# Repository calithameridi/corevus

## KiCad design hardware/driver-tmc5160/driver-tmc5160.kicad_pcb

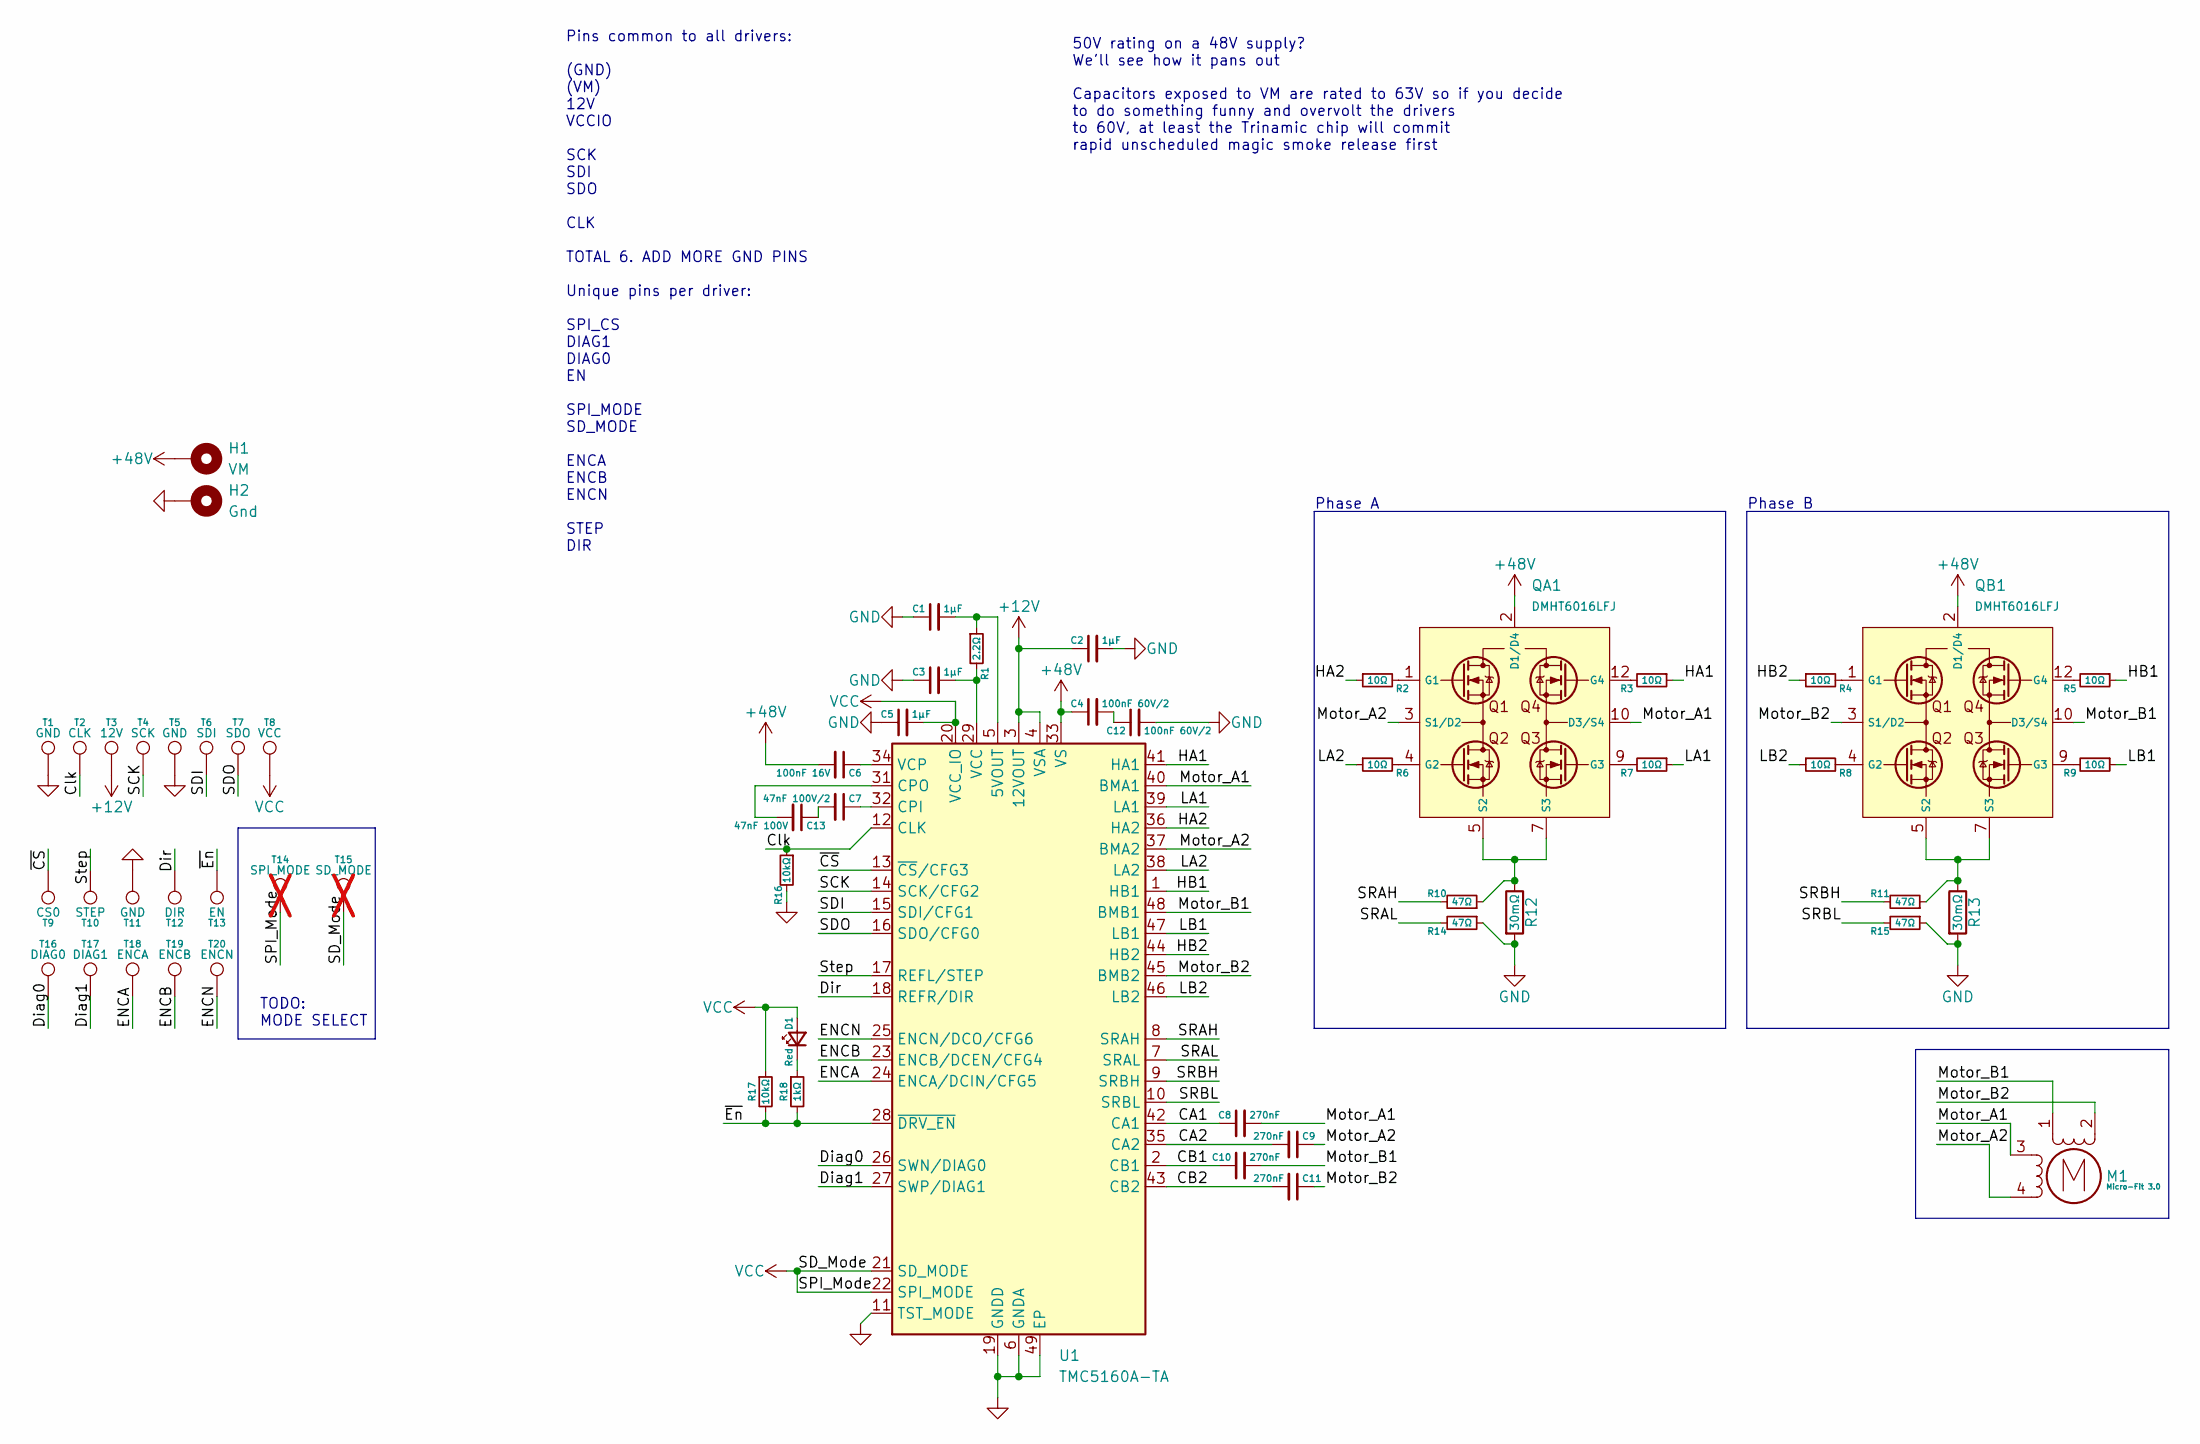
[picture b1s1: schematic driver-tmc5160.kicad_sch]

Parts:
C1, C2: 1μF; 0402C
C3, C5: 1µF; 0402C
C4, C12: 100nF 60V/2; 0402C
C6: 100nF 16V; 0402C
C7: 47nF 100V/2; 0402C
C8, C9, C10, C11: 270nF; 0402C
C13: 47nF 100V; 0402C
D1: Red; 0603LED
H1: VM; MountingHole_M3_Driver
H2: Gnd; MountingHole_M3_Driver
M1: Micro-Fit 3.0; XKB_X3025WRS-04D
QA1: DMHT6016LFJ; V-DFN5045-12-Type-B; LCSC C460986
QB1: DMHT6016LFJ; V-DFN5045-12-Type-B; LCSC C460986
R1: 2.2Ω; 0402R
R2, R3, R4, R5, R6, R7, R8, R9: 10Ω; 0402R
R10, R11, R14, R15: 47Ω; 0402R
R12, R13: 30mΩ; R_1206_3216Metric
R16, R17: 10kΩ; 0402R
R18: 1kΩ; 0402R
T1, T5, T11: GND; LGA_Land
T2: CLK; LGA_Land
T3: 12V; LGA_Land
T4: SCK; LGA_Land
T6: SDI; LGA_Land
T7: SDO; LGA_Land
T8: VCC; LGA_Land
T9: CS0; LGA_Land
T10: STEP; LGA_Land
T12: DIR; LGA_Land
T13: EN; LGA_Land
T14: SPI_MODE; LGA_Land; not fitted
T15: SD_MODE; LGA_Land; not fitted
T16: DIAG0; LGA_Land
T17: DIAG1; LGA_Land
T18: ENCA; LGA_Land
T19: ENCB; LGA_Land
T20: ENCN; LGA_Land
U1: TMC5160A-TA; TQFP-48-1EP_7x7mm_P0.5mm_EP5x5mm_ThermalVias

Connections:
+12V: C2.1, T3.1, U1.3 (12VOUT), U1.4 (VSA)
+48V: C4.1, C6.2, H1.1, QA1.2 (D1/D4), QA1.11 (D1/D4), QA1.P1 (D1/D4), QB1.2 (D1/D4), QB1.11 (D1/D4), QB1.P1 (D1/D4), U1.33 (VS)
/CA1: C8.1, U1.42 (CA1)
/CA2: C9.2, U1.35 (CA2)
/CB1: C10.1, U1.2 (CB1)
/CB2: C11.2, U1.43 (CB2)
/Clk: R16.1, T2.1, U1.12 (CLK)
/Diag0: T16.1, U1.26 (SWN/DIAG0)
/Diag1: T17.1, U1.27 (SWP/DIAG1)
/Dir: T12.1, U1.18 (REFR/DIR)
/ENCA: T18.1, U1.24 (ENCA/DCIN/CFG5)
/ENCB: T19.1, U1.23 (ENCB/DCEN/CFG4)
/ENCN: T20.1, U1.25 (ENCN/DCO/CFG6)
/HA1: R3.1, U1.41 (HA1)
/HA2: R2.1, U1.36 (HA2)
/HB1: R5.1, U1.1 (HB1)
/HB2: R4.1, U1.44 (HB2)
/LA1: R7.1, U1.39 (LA1)
/LA2: R6.1, U1.38 (LA2)
/LB1: R9.1, U1.47 (LB1)
/LB2: R8.1, U1.46 (LB2)
/Motor_A1: C8.2, M1.3, QA1.10 (D3/S4), QA1.P3 (D3/S4), U1.40 (BMA1)
/Motor_A2: C9.1, M1.4, QA1.3 (S1/D2), QA1.P2 (S1/D2), U1.37 (BMA2)
/Motor_B1: C10.2, M1.1, QB1.10 (D3/S4), QB1.P3 (D3/S4), U1.48 (BMB1)
/Motor_B2: C11.1, M1.2 (-), QB1.3 (S1/D2), QB1.P2 (S1/D2), U1.45 (BMB2)
/SCK: T4.1, U1.14 (SCK/CFG2)
/SDI: T6.1, U1.15 (SDI/CFG1)
/SDO: T7.1, U1.16 (SDO/CFG0)
/SRAH: R10.2, U1.8 (SRAH)
/SRAL: R14.2, U1.7 (SRAL)
/SRBH: R11.2, U1.9 (SRBH)
/SRBL: R15.2, U1.10 (SRBL)
/Step: T10.1, U1.17 (REFL/STEP)
/~CS: T9.1, U1.13 (~CS/CFG3)
/~En: R17.2, R18.2, T13.1, U1.28 (~DRV_EN)
GND: C1.1, C2.2, C3.1, C5.1, C12.2, H2.1, R12.2, R13.2, R14.1, R15.1, R16.2, T1.1, T5.1, T11.1, U1.6 (GNDA), U1.11 (TST_MODE), U1.19 (GNDD), U1.30 (GNDD), U1.49 (EP)
unnamed: C4.2, C12.1
unnamed: C7.2, C13.1
unnamed: D1.1 (K), R18.1
unnamed: QA1.1 (G1), R2.2
unnamed: QA1.4 (G2), R6.2
unnamed: QA1.9 (G3), R7.2
unnamed: QA1.12 (G4), R3.2
unnamed: QA1.5 (S2), QA1.6 (S2), QA1.7 (S3), QA1.8 (S3), R10.1, R12.1
unnamed: QB1.1 (G1), R4.2
unnamed: QB1.4 (G2), R8.2
unnamed: QB1.9 (G3), R9.2
unnamed: QB1.12 (G4), R5.2
unnamed: QB1.5 (S2), QB1.6 (S2), QB1.7 (S3), QB1.8 (S3), R11.1, R13.1
unnamed: C1.2, R1.1, U1.5 (5VOUT)
unnamed: C7.1, U1.32 (CPI)
unnamed: C13.2, U1.31 (CPO)
unnamed: C3.2, R1.2, U1.29 (VCC)
unnamed: C6.1, U1.34 (VCP)
VCC: C5.2, D1.2 (A), R17.1, T8.1, T14.1, T15.1, U1.20 (VCC_IO), U1.21 (SD_MODE), U1.22 (SPI_MODE)

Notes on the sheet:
50V rating on a 48V supply? We'll see how it pans out
Phase A
Phase B
Capacitors exposed to VM are rated to 63V so if you decide to do something funny and overvolt the drivers to 60V, at least the Trinamic chip will commit rapid unscheduled magic smoke release first
TODO: MODE SELECT
Pins common to all drivers: (GND) (VM) 12V VCCIO SCK SDI SDO CLK TOTAL 6. ADD MORE GND PINS Unique pins per driver: SPI_CS DIAG1 DIAG0 EN SPI_MODE SD_MODE ENCA ENCB ENCN STEP DIR

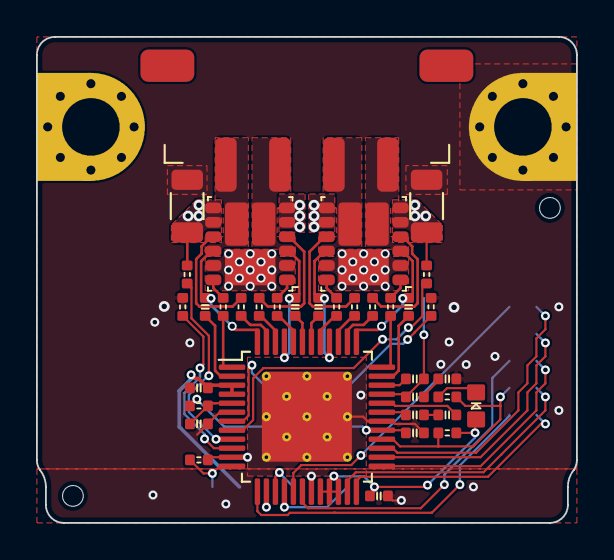
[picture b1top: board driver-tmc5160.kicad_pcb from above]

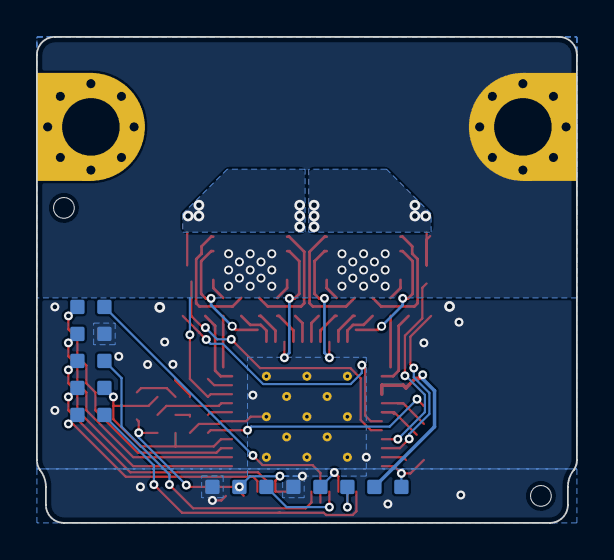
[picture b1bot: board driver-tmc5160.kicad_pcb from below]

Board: 2 copper layers, 30.0 x 27.0 mm, 56 parts (18 on the bottom side), 55 nets.

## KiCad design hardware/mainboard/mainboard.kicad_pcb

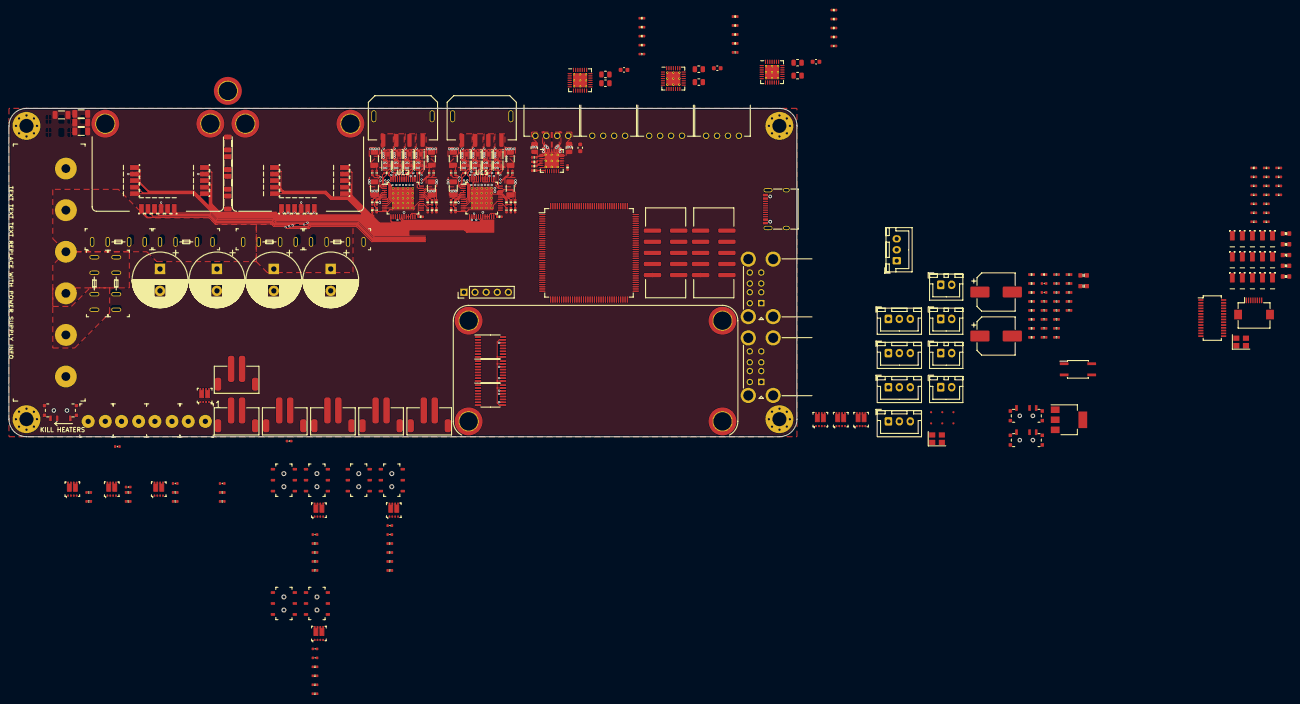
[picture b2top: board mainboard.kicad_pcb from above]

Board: 4 copper layers, 180.0 x 75.0 mm, 331 parts (0 on the bottom side), 217 nets.

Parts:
C1, C2: 20pF; 0402C
C3, C4, C42, C45, C57, C60: 2.2μF; 0402C
C5, C44, C46, C59, C61: 100nF 50V; 0402C
C6, C7, C8, C9, C19, C24, C29, C34: 1μF; 0402C
C10, C11: 10μF; 0603C
C12, C15: 220μF 35V; CP_Elec_8x10.5
C13, C14, C16, C17: 470μF 63V; CP_Radial_D12.5mm_P5.00mm
C18, C23, C28, C33, C76: 100nF; 0402C
C20, C25, C30, C35, C39, C54: 100nF 16V; 0402C
C21, C26, C31, C36: 22nF 50V; 0402C
C22, C27, C32, C37: 1μF 50V; C_0603_1608Metric
C38, C40, C53, C55: 47nF 50V; 0402C
C41, C43, C56, C58: 470nF; 0402C
C47, C48, C49, C50, C62, C63, C64, C65: 220nF; 0402C
C51, C52, C66, C67: 1μF 100V; C_1206_3216Metric
C68, C69, C70, C71, C72, C73, C74, C75: 1μF 63V; C_1206_3216Metric
D1, D2, D3, D4, D5, D6, D7, D8, D9, D10, D11, D12: Red; 0402LED
D13: P4; 0603LED
D14: P2; 0603LED
D15: P3; 0603LED
D16: P1; 0603LED
D17: Red; 0603LED
F1, F2, F3, F4, F5, F6: 10A; XF-505P
FID1, FID2, FID3, FID4, FID5, FID6: Fiducial; Fiducial_0.5mm_Mask1mm
H1, H2, H3, H4: MountingHole; MountingHole_3.2mm_M3_Pad_Via
H5, H5#2, H7: V_{M}; M3_M2.5_PCB_Nut
H6, H8: Gnd; M3_M2.5_PCB_Nut
H9, H10, H11, H12: M2.5; M3_M2.5_PCB_Nut
J1: USB 2.0; USB_C_Receptacle_XKB_U262-16XN-4BVC11
J2, J4, J5, J6, J7: JST XH; JST_XH_B3B-XH-A_1x03_P2.50mm_Vertical
J3: Power In; DBT50G-9.5-6P
J8, J9, J10, J11: JST XH; JST_XH_B2B-XH-A_1x02_P2.50mm_Vertical
J12: EXP1; IDC-Header_2x05_P2.54mm_Vertical_SMD
J13: EXP2; IDC-Header_2x05_P2.54mm_Vertical_SMD
J14, J15, J16, J17, J18, J19: JST XH; ShouHan_2.54-2PLT
J20, J21, J22, J23: Screw_Terminal_01x02; DB125-3.81-2P
J24: Conn_01x05_Pin; PinHeader_1x05_P2.54mm_Vertical
J25: FPC 8p 0.5mm; Hirose_FH12-8S-0.5SH_1x08-1MP_P0.50mm_Horizontal
J26, J27: USB_A_Stacked; USB_A_CUI_UJ2-ADH-TH_Horizontal_Stacked
M1, M2, M3, M4: JST XH; XKB_X8821WR-04S
M5, M6: Micro-Fit 3.0; XKB_X3025WRS-04C
Q1, Q2, Q3, Q20, Q21, Q22, Q23, Q24, Q25, Q26: AGM308MBP
Q4, Q5, Q6, Q7, Q8, Q9, Q10, Q11, Q12, Q13, Q14, Q15, Q16, Q17, Q18, Q19: DMT6016LFDF
R1, R14, R19, R22, R25, R28, R31, R39, R49, R50, R53, R54, R57, R58, R60, R62, R64, R66, R67, R71: 10kΩ; 0402R
R2, R73, R74, R83: 330Ω; 0402R
R3, R11: 100kΩ; 0402R
R4, R5, R69, R70, R75, R76, R77, R78, R79, R80, R81, R82: 33Ω; 0402R
R6, R7: 5.1kΩ; 0402R
R8, R9: 200kΩ; 0402R
R10, R12, R13, R47, R48, R51, R52, R55, R56, R59, R61, R63, R65: 1kΩ; 0402R
R15, R16, R17, R18: 4.7kΩ; 0402R
R20, R21, R23, R24, R26, R27, R29, R30: 100mΩ; R_0805_2012Metric
R32, R40: 2.2Ω; 0402R
R33, R34, R36, R37, R41, R42, R44, R45: 47Ω; 0402R
R35, R38, R43, R46: 33mΩ; R_1206_3216Metric
R68: 300Ω; 0402R
R72: 2.4kΩ; 0402R
SW1, SW2, SW9: SW_SPDT; MSS12C02-LS
SW3, SW4, SW5, SW6, SW7, SW8: SPDT, 2A; MS-22C01_SPDT
T1, T17: V_{SA}; LGA_Spring
T2, T18: SClk; LGA_Spring
T3, T19: Gnd; LGA_Spring
T4, T20: MOSI; LGA_Spring
T5, T21: MISO; LGA_Spring
T6, T22: V_{CC}IO; LGA_Spring
T7, T8, T9, T10, T11, T12, T13, T14, T15, T16, T23, T24, T25, T26, T27, T28, T29, T30, T31, T32: TestPoint; LGA_Spring
T33, T34: 5V; LGA_Spring_3.5x1
T35, T39: Gnd; LGA_Spring_3.5x1
T36: TXD; LGA_Spring_3.5x1
T37: RXD; LGA_Spring_3.5x1
T38: V_{CC}; LGA_Spring_3.5x1
T40: MOSI; LGA_Spring_3.5x1
T41: MISO; LGA_Spring_3.5x1
T42: CS; LGA_Spring_3.5x1
T43: SClk; LGA_Spring_3.5x1
T44: Shield; LGA_Spring_3.5x1
T45: D+; LGA_Spring_3.5x1
T46: D-; LGA_Spring_3.5x1
T47: 5VDet; LGA_Spring_3.5x1
U1: STM32F407ZETx; LQFP-144_20x20mm_P0.5mm
U2, U3, U4: CD40109B; TSSOP-16_4.4x5mm_P0.65mm
U5: LTV-357T; SO-4_4.4x3.6mm_P2.54mm
U6: AMS1117-3.3; SOT-223-3_TabPin2
U7, U8, U9, U10: TMC2208-LA; TQFN-28-1EP_5x5mm_P0.5mm_EP3.25x3.25mm_ThermalVias
U11, U12: TMC5160A-TA; TMCx160
U13: USB2 Hub; SSOP-28_3.9x9.9mm_P0.635mm
Y1: 12 MHz; Crystal_SMD_3225-4Pin_3.2x2.5mm
Y2: 12MHz; Crystal_SMD_3225-4Pin_3.2x2.5mm

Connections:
+3.3V: C11.1, C18.1, C23.1, C28.1, C33.1, C41.2, C56.2, C76.2, J4.1, J5.1, J6.1, J7.1, R12.2, R15.2, R16.2, R17.2, R18.2, R71.2, SW1.3 (C), T6.1, T22.1, U1.6 (VBAT), U1.17 (VDD), U1.30 (VDD), U1.32 (VREF+), U1.33 (VDDA), U1.39 (VDD), U1.52 (VDD), U1.62 (VDD), U1.72 (VDD), U1.84 (VDD), U1.95 (VDD), U1.108 (VDD), U1.121 (VDD), U1.131 (VDD), U1.144 (VDD), U2.1 (V_{CC}), U2.2 (En_{A}), U2.7 (En_{B}), U3.1 (V_{CC}), U3.2 (En_{A}), U3.7 (En_{B}), U4.1 (V_{CC}), U4.2 (En_{A}), U4.7 (En_{B}), U6.2 (VO), U7.9 (MS1), U7.10 (MS2), U7.15 (Vcc_IO), U8.9 (MS1), U8.10 (MS2), U8.15 (Vcc_IO), U9.9 (MS1), U9.10 (MS2), U9.15 (Vcc_IO), U10.9 (MS1), U10.10 (MS2), U10.15 (Vcc_IO), U11.20 (VCC_IO), U11.21 (SD_MODE), U11.22 (SPI_MODE), U12.20 (VCC_IO), U12.21 (SD_MODE), U12.22 (SPI_MODE), U13.19 (BusJ), U13.21 (VD33F), U13.26 (OVCJ)
+5V: C10.1, J12.10, J13.10, J24.1, J24.2, J26.1 (VBUS1), J26.5 (VBUS2), J27.1 (VBUS1), J27.5 (VBUS2), SW2.1 (A), T33.1, T34.1, U6.3 (VI)
+12V: C45.2, C60.2, SW3.1 (A), SW4.3 (C), SW5.1 (A), SW6.3 (C), SW7.1 (A), SW8.3 (C), T1.1, T17.1, U2.16 (V_{DD}), U3.16 (V_{DD}), U4.16 (V_{DD}), U11.3 (12VOUT), U11.4 (VSA), U12.3 (12VOUT), U12.4 (VSA)
+24V: C12.1, C15.1, C20.2, C22.2, C25.2, C27.2, C30.2, C32.2, C35.2, C37.2, F6.2, J20.1, J21.1, J22.1, J23.1, R8.1, SW2.3 (C), SW3.3 (C), SW4.1 (A), SW5.3 (C), SW6.1 (A), SW7.3 (C), SW8.1 (A), U7.22 (VS), U7.28 (VS), U8.22 (VS), U8.28 (VS), U9.22 (VS), U9.28 (VS), U10.22 (VS), U10.28 (VS)
/BG: D2.2 (A), Q1.2 (G), Q1.4 (G), Q2.2 (G), Q2.4 (G), Q3.2 (G), Q3.4 (G), R14.1, U4.13 (H)
/BOOT0: D1.2 (A), R1.1, SW1.2 (B), U1.138 (BOOT0)
/Bed_H+: F3.2, J3.5
/Bed_H-: J3.6, Q1.5 (D), Q1.6 (D), Q1.7 (D), Q1.8 (D), Q2.5 (D), Q2.6 (D), Q2.7 (D), Q2.8 (D), Q3.5 (D), Q3.6 (D), Q3.7 (D), Q3.8 (D)
/Fan0_Gate: D5.2 (A), Q21.4 (G), R53.1, U4.4 (E)
/Fan1_Gate: D6.2 (A), Q21.2 (G), R54.1, U4.5 (F)
/Fan2_Gate: D3.2 (A), Q20.4 (G), R49.1, U3.4 (E)
/Fan3_Gate: D4.2 (A), Q20.2 (G), R50.1, U3.5 (F)
/Fan4_Gate: D7.2 (A), Q22.4 (G), R57.1, U2.4 (E)
/Fan5_Gate: D8.2 (A), Q22.2 (G), R58.1, U2.5 (F)
/HE0_Gate: D10.2 (A), Q24.2 (G), Q24.4 (G), R62.1, U3.13 (H)
/HE1_Gate: D9.2 (A), Q23.2 (G), Q23.4 (G), R60.1, U3.11 (G)
/HE2_Gate: D11.2 (A), Q25.2 (G), Q25.4 (G), R64.1, U2.13 (H)
/HE3_Gate: D12.2 (A), Q26.2 (G), Q26.4 (G), R66.1, U2.11 (G)
/HeEn: U2.9 (En_{C}), U2.15 (En_{D}), U3.9 (En_{C}), U3.15 (En_{D}), U4.9 (En_{C}), U4.15 (En_{D})
/MISO_{3}: J13.1, T4.1, T20.1, U11.15 (SDI/CFG1), U12.15 (SDI/CFG1)
/MOSI_{3}: J13.6, T5.1, T21.1, U11.16 (SDO/CFG0), U12.16 (SDO/CFG0)
/Motor 0 (TMC2208)/A1: M1.2 (-), U7.24 (OA1)
/Motor 0 (TMC2208)/A2: M1.1, U7.21 (OA2)
/Motor 0 (TMC2208)/B1: M1.3, U7.26 (OB1)
/Motor 0 (TMC2208)/B2: M1.4, U7.1 (OB2)
/Motor 0 (TMC2208)/BRA: R20.1, U7.23 (BRA)
/Motor 0 (TMC2208)/BRB: R21.1, U7.27 (BRB)
/Motor 1 (TMC2208)/A1: M2.2 (-), U8.24 (OA1)
/Motor 1 (TMC2208)/A2: M2.1, U8.21 (OA2)
/Motor 1 (TMC2208)/B1: M2.3, U8.26 (OB1)
/Motor 1 (TMC2208)/B2: M2.4, U8.1 (OB2)
/Motor 1 (TMC2208)/BRA: R23.1, U8.23 (BRA)
/Motor 1 (TMC2208)/BRB: R24.1, U8.27 (BRB)
/Motor 2 (TMC2208)/A1: M3.2 (-), U9.24 (OA1)
/Motor 2 (TMC2208)/A2: M3.1, U9.21 (OA2)
/Motor 2 (TMC2208)/B1: M3.3, U9.26 (OB1)
/Motor 2 (TMC2208)/B2: M3.4, U9.1 (OB2)
/Motor 2 (TMC2208)/BRA: R26.1, U9.23 (BRA)
/Motor 2 (TMC2208)/BRB: R27.1, U9.27 (BRB)
/Motor 3 (TMC2208)/A1: M4.2 (-), U10.24 (OA1)
/Motor 3 (TMC2208)/A2: M4.1, U10.21 (OA2)
/Motor 3 (TMC2208)/B1: M4.3, U10.26 (OB1)
/Motor 3 (TMC2208)/B2: M4.4, U10.1 (OB2)
/Motor 3 (TMC2208)/BRA: R29.1, U10.23 (BRA)
/Motor 3 (TMC2208)/BRB: R30.1, U10.27 (BRB)
/Motor 4 (TMCx160)/CA1: C47.1, U11.42 (CA1)
/Motor 4 (TMCx160)/CA2: C49.2, U11.35 (CA2)
/Motor 4 (TMCx160)/CB1: C48.1, U11.2 (CB1)
/Motor 4 (TMCx160)/CB2: C50.2, U11.43 (CB2)
/Motor 4 (TMCx160)/HA1: Q6.3 (G), U11.41 (HA1)
/Motor 4 (TMCx160)/HA2: Q4.3 (G), U11.36 (HA2)
/Motor 4 (TMCx160)/HB1: Q10.3 (G), U11.1 (HB1)
/Motor 4 (TMCx160)/HB2: Q8.3 (G), U11.44 (HB2)
/Motor 4 (TMCx160)/LA1: Q7.3 (G), U11.39 (LA1)
/Motor 4 (TMCx160)/LA2: Q5.3 (G), U11.38 (LA2)
/Motor 4 (TMCx160)/LB1: Q11.3 (G), U11.47 (LB1)
/Motor 4 (TMCx160)/LB2: Q9.3 (G), U11.46 (LB2)
/Motor 4 (TMCx160)/Motor_A1: C47.2, M5.3, Q6.4 (S), Q6.7 (S), Q7.1 (D), Q7.2 (D), Q7.5 (D), Q7.6 (D), Q7.8 (D), U11.40 (BMA1)
/Motor 4 (TMCx160)/Motor_A2: C49.1, M5.4, Q4.4 (S), Q4.7 (S), Q5.1 (D), Q5.2 (D), Q5.5 (D), Q5.6 (D), Q5.8 (D), U11.37 (BMA2)
/Motor 4 (TMCx160)/Motor_B1: C48.2, M5.1, Q10.4 (S), Q10.7 (S), Q11.1 (D), Q11.2 (D), Q11.5 (D), Q11.6 (D), Q11.8 (D), U11.48 (BMB1)
/Motor 4 (TMCx160)/Motor_B2: C50.1, M5.2 (-), Q8.4 (S), Q8.7 (S), Q9.1 (D), Q9.2 (D), Q9.5 (D), Q9.6 (D), Q9.8 (D), U11.45 (BMB2)
/Motor 4 (TMCx160)/SRAH: R33.2, U11.8 (SRAH)
/Motor 4 (TMCx160)/SRAL: R34.2, U11.7 (SRAL)
/Motor 4 (TMCx160)/SRBH: R36.2, U11.9 (SRBH)
/Motor 4 (TMCx160)/SRBL: R37.2, U11.10 (SRBL)
/Motor 5 (TMCx160)/CA1: C62.1, U12.42 (CA1)
/Motor 5 (TMCx160)/CA2: C64.2, U12.35 (CA2)
/Motor 5 (TMCx160)/CB1: C63.1, U12.2 (CB1)
/Motor 5 (TMCx160)/CB2: C65.2, U12.43 (CB2)
/Motor 5 (TMCx160)/HA1: Q14.3 (G), U12.41 (HA1)
/Motor 5 (TMCx160)/HA2: Q12.3 (G), U12.36 (HA2)
/Motor 5 (TMCx160)/HB1: Q18.3 (G), U12.1 (HB1)
/Motor 5 (TMCx160)/HB2: Q16.3 (G), U12.44 (HB2)
/Motor 5 (TMCx160)/LA1: Q15.3 (G), U12.39 (LA1)
/Motor 5 (TMCx160)/LA2: Q13.3 (G), U12.38 (LA2)
/Motor 5 (TMCx160)/LB1: Q19.3 (G), U12.47 (LB1)
/Motor 5 (TMCx160)/LB2: Q17.3 (G), U12.46 (LB2)
/Motor 5 (TMCx160)/Motor_A1: C62.2, M6.3, Q14.4 (S), Q14.7 (S), Q15.1 (D), Q15.2 (D), Q15.5 (D), Q15.6 (D), Q15.8 (D), U12.40 (BMA1)
/Motor 5 (TMCx160)/Motor_A2: C64.1, M6.4, Q12.4 (S), Q12.7 (S), Q13.1 (D), Q13.2 (D), Q13.5 (D), Q13.6 (D), Q13.8 (D), U12.37 (BMA2)
/Motor 5 (TMCx160)/Motor_B1: C63.2, M6.1, Q18.4 (S), Q18.7 (S), Q19.1 (D), Q19.2 (D), Q19.5 (D), Q19.6 (D), Q19.8 (D), U12.48 (BMB1)
/Motor 5 (TMCx160)/Motor_B2: C65.1, M6.2 (-), Q16.4 (S), Q16.7 (S), Q17.1 (D), Q17.2 (D), Q17.5 (D), Q17.6 (D), Q17.8 (D), U12.45 (BMB2)
/Motor 5 (TMCx160)/SRAH: R41.2, U12.8 (SRAH)
/Motor 5 (TMCx160)/SRAL: R42.2, U12.7 (SRAL)
/Motor 5 (TMCx160)/SRBH: R44.2, U12.9 (SRBH)
/Motor 5 (TMCx160)/SRBL: R45.2, U12.10 (SRBL)
/Pi Zero + USB Hub/5VDet: R67.2, T47.1, U13.18 (VBusM)
/Pi Zero + USB Hub/D1+: R75.2, U13.11 (DP1)
/Pi Zero + USB Hub/D1-: R76.2, U13.10 (DM1)
/Pi Zero + USB Hub/D2+: R77.2, U13.9 (DP2)
/Pi Zero + USB Hub/D2-: R78.2, U13.8 (DM2)
/Pi Zero + USB Hub/D3+: R79.2, U13.7 (DP3)
/Pi Zero + USB Hub/D3-: R80.2, U13.6 (DM3)
/Pi Zero + USB Hub/D4+: R81.2, U13.5 (DP4)
/Pi Zero + USB Hub/D4-: R82.2, U13.4 (DM4)
/Pi Zero + USB Hub/DU+: R69.2, T45.1
/Pi Zero + USB Hub/DU-: R70.2, T46.1
/Pi Zero + USB Hub/RXD: J24.5, T37.1
/Pi Zero + USB Hub/TXD: J24.4, T36.1
/Probe: R11.1, U5.3
/SClk_{3}: J13.2, T2.1, T18.1, U11.14 (SCK/CFG2), U12.14 (SCK/CFG2)
/Th_{0}: C6.2, J8.1, R15.1
/Th_{1}: C7.2, J9.1, R16.1
/Th_{2}: C8.2, J10.1, R17.1
/Th_{3}: C9.2, J11.1, R18.1
/_{M0}~En: R19.2, U7.2 (~En)
/_{M1}~En: R22.2, U8.2 (~En)
/_{M2}~En: R25.2, U9.2 (~En)
/_{M3}~En: R28.2, U10.2 (~En)
/_{M4}~En: R31.2, U11.28 (~DRV_EN)
/_{M5}~En: R39.2, U12.28 (~DRV_EN)
GND: C1.1, C2.1, C3.2, C4.2, C5.2, C6.1, C7.1, C8.1, C9.1, C10.2, C11.2, C12.2, C13.2, C14.2, C15.2, C16.2, C17.2, C18.2, C19.1, C22.1, C23.2, C24.1, C27.1, C28.2, C29.1, C32.1, C33.2, C34.1, C37.1, C41.1, C42.1, C43.1, C45.1, C46.2, C51.2, C52.2, C56.1, C57.1, C58.1, C60.1, C61.2, C66.2, C67.2, C68.2, C69.2, C70.2, C71.2, C72.2, C73.2, C74.2, C75.2, C76.1, H6.1, H8.1, H9.1, H10.1, H11.1, H12.1, J1.A1 (GND), J1.A12 (GND), J1.B1 (GND), J1.B12 (GND), J1.S1 (SHIELD), J2.2, J3.1, J3.3, J4.2, J5.2, J6.2, J7.2, J8.2, J9.2, J10.2, J11.2, J12.9, J13.9, J24.3, J25.1, J26.4 (GND1), J26.8 (GND2), J26.9 (Shield), J27.4 (GND1), J27.8 (GND2), J27.9 (Shield), Q1.1 (S), Q1.3 (S), Q2.1 (S), Q2.3 (S), Q3.1 (S), Q3.3 (S), Q20.1 (S), Q20.3 (S), Q21.1 (S), Q21.3 (S), Q22.1 (S), Q22.3 (S), Q23.1 (S), Q23.3 (S), Q24.1 (S), Q24.3 (S), Q25.1 (S), Q25.3 (S), Q26.1 (S), Q26.3 (S), R1.2, R2.1, R6.1, R7.1, R8.2, R9.2, R11.2, R13.2, R14.2, R19.1, R20.2, R21.2, R22.1, R23.2, R24.2, R25.1, R26.2, R27.2, R28.1, R29.2, R30.2, R31.1, R34.1, R35.2, R37.1, R38.2, R39.1, R42.1, R43.2, R45.1, R46.2, R47.2, R48.2, R49.2, R50.2, R51.2, R52.2, R53.2, R54.2, R55.2, R56.2, R57.2, R58.2, R59.2, R60.2, R61.2, R62.2, R63.2, R64.2, R65.2, R66.2, R67.1, R68.2, R83.1, SW1.1 (A), T3.1, T9.1, T10.1, T19.1, T25.1, T26.1, T35.1, T39.1, T44.1, U1.16 (VSS), U1.31 (VSSA), U1.38 (VSS), U1.51 (VSS), U1.61 (VSS), U1.83 (VSS), U1.94 (VSS), U1.107 (VSS), U1.120 (VSS), U1.130 (VSS), U2.8 (V_{SS}), U3.8 (V_{SS}), U4.8 (V_{SS}), U5.2, U6.1 (GND), U7.3 (Gnd), U7.7 (NC), U7.18 (Gnd), U7.20 (NC), U7.25 (NC), U7.29 (Pad), U8.3 (Gnd), U8.7 (NC), U8.18 (Gnd), U8.20 (NC), U8.25 (NC), U8.29 (Pad), U9.3 (Gnd), U9.7 (NC), U9.18 (Gnd), U9.20 (NC), U9.25 (NC), U9.29 (Pad), U10.3 (Gnd), U10.7 (NC), U10.18 (Gnd), U10.20 (NC), U10.25 (NC), U10.29 (Pad), U11.6 (GNDA), U11.11 (TST_MODE), U11.19 (GNDD), U11.30 (GNDD), U11.49 (EP), U12.6 (GNDA), U12.11 (TST_MODE), U12.19 (GNDD), U12.30 (GNDD), U12.49 (EP), U13.1 (VSS), Y1.2, Y1.4, Y2.2, Y2.4
unnamed: C38.1, C40.2
unnamed: C44.2, C46.1
unnamed: C53.1, C55.2
unnamed: C59.2, C61.1
unnamed: D1.1 (K), R2.2
unnamed: D2.1 (K), R13.1
unnamed: D3.1 (K), R47.1
unnamed: D4.1 (K), R48.1
unnamed: D5.1 (K), R51.1
unnamed: D6.1 (K), R52.1
unnamed: D7.1 (K), R55.1
unnamed: D8.1 (K), R56.1
unnamed: D9.1 (K), R59.1
unnamed: D10.1 (K), R61.1
unnamed: D11.1 (K), R63.1
unnamed: D12.1 (K), R65.1
unnamed: D13.2 (A), D14.1 (K), R73.1
unnamed: D13.1 (K), D14.2 (A), D15.1 (K), D16.2 (A), D17.2 (A), U13.22 (DRV)
unnamed: D15.2 (A), D16.1 (K), R74.1
unnamed: D17.1 (K), R83.2
unnamed: J1.A5 (CC1), R6.2
unnamed: J1.B5 (CC2), R7.2
unnamed: J1.A6 (D+), J1.B6 (D+), R5.2
unnamed: J1.A7 (D-), J1.B7 (D-), R4.2
unnamed: C5.1, J2.1, SW2.2 (B)
unnamed: J2.3, R10.1
unnamed: F1.1, F4.1, J3.2
unnamed: F2.1, F3.1, F5.1, F6.1, J3.4
unnamed: J14.1, SW3.2 (B)
unnamed: J14.2, Q20.5 (D), Q20.6 (D)
unnamed: J15.1, SW4.2 (B)
unnamed: J15.2, Q20.7 (D), Q20.8 (D)
unnamed: J16.1, SW5.2 (B)
unnamed: J16.2, Q21.5 (D), Q21.6 (D)
unnamed: J17.1, SW6.2 (B)
unnamed: J17.2, Q21.7 (D), Q21.8 (D)
unnamed: J18.1, SW7.2 (B)
unnamed: J18.2, Q22.5 (D), Q22.6 (D)
unnamed: J19.1, SW8.2 (B)
unnamed: J19.2, Q22.7 (D), Q22.8 (D)
unnamed: J20.2, Q23.5 (D), Q23.6 (D), Q23.7 (D), Q23.8 (D)
unnamed: J21.2, Q24.5 (D), Q24.6 (D), Q24.7 (D), Q24.8 (D)
unnamed: J22.2, Q25.5 (D), Q25.6 (D), Q25.7 (D), Q25.8 (D)
unnamed: J23.2, Q26.5 (D), Q26.6 (D), Q26.7 (D), Q26.8 (D)
unnamed: J25.2, T38.1
unnamed: J25.3, T42.1
unnamed: J25.6, T41.1
unnamed: J25.7, T40.1
unnamed: J25.8, T43.1
unnamed: J26.3 (D1+), R77.1
unnamed: J26.2 (D1-), R78.1
unnamed: J26.7 (D2+), R75.1
unnamed: J26.6 (D2-), R76.1
unnamed: J27.3 (D1+), R81.1
unnamed: J27.2 (D1-), R82.1
unnamed: J27.7 (D2+), R79.1
unnamed: J27.6 (D2-), R80.1
unnamed: Q5.4 (S), Q5.7 (S), Q7.4 (S), Q7.7 (S), R33.1, R35.1
unnamed: Q9.4 (S), Q9.7 (S), Q11.4 (S), Q11.7 (S), R36.1, R38.1
unnamed: Q13.4 (S), Q13.7 (S), Q15.4 (S), Q15.7 (S), R41.1, R43.1
unnamed: Q17.4 (S), Q17.7 (S), Q19.4 (S), Q19.7 (S), R44.1, R46.1
unnamed: R10.2, U5.1
unnamed: R12.1, U5.4
unnamed: R68.1, R72.2
unnamed: R4.1, U1.103 (PA11)
unnamed: R5.1, U1.104 (PA12)
unnamed: C1.2, R3.1, U1.23 (PH0), Y1.1
unnamed: C2.2, R3.2, U1.24 (PH1), Y1.3
unnamed: C4.1, U1.71 (VCAP_1)
unnamed: C3.1, U1.106 (VCAP_2)
unnamed: C19.2, U7.8 (5VOut)
unnamed: C21.2, U7.5 (CPI)
unnamed: C21.1, U7.4 (CPO)
unnamed: C20.1, U7.6 (VCP)
unnamed: C24.2, U8.8 (5VOut)
unnamed: C26.2, U8.5 (CPI)
unnamed: C26.1, U8.4 (CPO)
unnamed: C25.1, U8.6 (VCP)
unnamed: C29.2, U9.8 (5VOut)
unnamed: C31.2, U9.5 (CPI)
unnamed: C31.1, U9.4 (CPO)
unnamed: C30.1, U9.6 (VCP)
unnamed: C34.2, U10.8 (5VOut)
unnamed: C36.2, U10.5 (CPI)
unnamed: C36.1, U10.4 (CPO)
unnamed: C35.1, U10.6 (VCP)
unnamed: C42.2, R32.1, U11.5 (5VOUT)
unnamed: C40.1, U11.32 (CPI)
unnamed: C38.2, U11.31 (CPO)
unnamed: C43.2, R32.2, U11.29 (VCC)
unnamed: C39.1, U11.34 (VCP)
unnamed: C57.2, R40.1, U12.5 (5VOUT)
unnamed: C55.1, U12.32 (CPI)
unnamed: C53.2, U12.31 (CPO)
unnamed: C58.2, R40.2, U12.29 (VCC)
unnamed: C54.1, U12.34 (VCP)
unnamed: R70.1, U13.15 (DMU)
unnamed: R69.1, U13.16 (DPU)
unnamed: R74.2, U13.23 (LED1)
unnamed: R73.2, U13.24 (LED2)
unnamed: R72.1, U13.14 (RExt)
unnamed: U13.3 (XIn), Y2.3
unnamed: U13.2 (XOut), Y2.1
unnamed: R71.1, U13.17 (XRstJ)
VMB: C13.1, C16.1, C39.2, C44.1, C51.1, C52.1, C54.2, C59.1, C66.1, C67.1, F4.2, F5.2, Q4.1 (D), Q4.2 (D), Q4.5 (D), Q4.6 (D), Q4.8 (D), Q6.1 (D), Q6.2 (D), Q6.5 (D), Q6.6 (D), Q6.8 (D), Q8.1 (D), Q8.2 (D), Q8.5 (D), Q8.6 (D), Q8.8 (D), Q10.1 (D), Q10.2 (D), Q10.5 (D), Q10.6 (D), Q10.8 (D), Q12.1 (D), Q12.2 (D), Q12.5 (D), Q12.6 (D), Q12.8 (D), Q14.1 (D), Q14.2 (D), Q14.5 (D), Q14.6 (D), Q14.8 (D), Q16.1 (D), Q16.2 (D), Q16.5 (D), Q16.6 (D), Q16.8 (D), Q18.1 (D), Q18.2 (D), Q18.5 (D), Q18.6 (D), Q18.8 (D), U11.33 (VS), U12.33 (VS)
VMC: C14.1, C17.1, C68.1, C69.1, C70.1, C71.1, C72.1, C73.1, C74.1, C75.1, F1.2, F2.2, H5#2.1, H7.1
